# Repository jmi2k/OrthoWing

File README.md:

OrthoWing
=========

- **dimensions**: 229.87mm × 128.27mm
- **layers**: 2

This is a Feather-compatible keyboard. It has a 5×12 ortholinear layout which
makes it very portable and a good fit for exotic use-cases (such as
macro-keyboards). The holes are designed for Cherry MX-compatible switches,
with no extra features.

Usage
-----

Both Feather sockets are interconnected, just like [Adafruit's FeatherWing
Doubler](https://www.adafruit.com/products/2890). The chip sockets hold two
MCP23017 I/O expanders, one on the left to select the column and one on the
right to get the keys pressed on each row for that column.

A controller Feather must also be attached, which scan the key matrix using
these two expanders through I²C. With the help of the second socket and
stacking headers, lots of FeatherWings can be added to provide additional
features!

Use cases
---------

Given a suitable controller (like this [Adafruit Feather
32u4](https://www.adafruit.com/product/2771)), it can be a regular USB
keyboard!

If you want something more exotic, I encourage you to try to push the limits
of the Feather interface! There are compatible displays, sensors, wireless
transceivers, even [quite powerful
FPGAs](https://github.com/gregdavill/OrangeCrab). The keyboard itself doesn't
use any GPIO pins, just the I²C pins (which are shared among all devices
attached), so these are all free.

License
-------

This project is licensed under the [Creative Commons Attribution-ShareAlike
4.0 International License](http://creativecommons.org/licenses/by-sa/4.0/).

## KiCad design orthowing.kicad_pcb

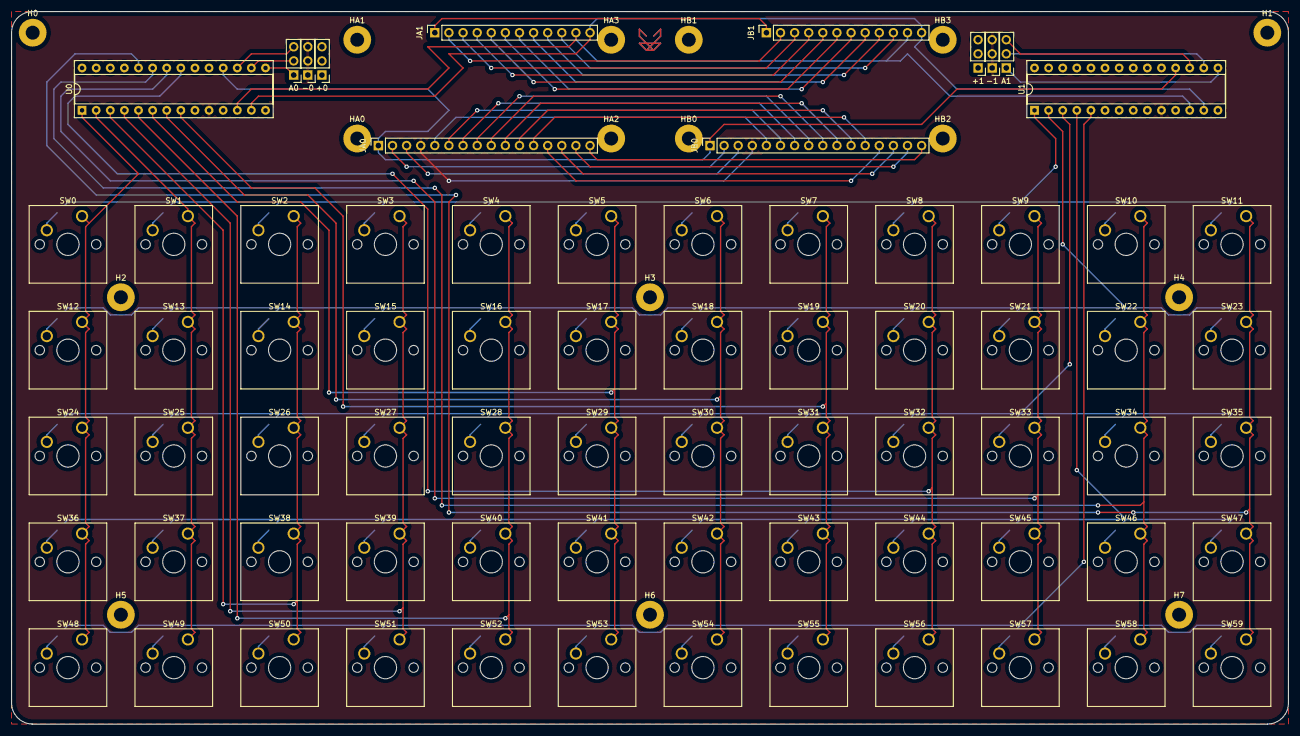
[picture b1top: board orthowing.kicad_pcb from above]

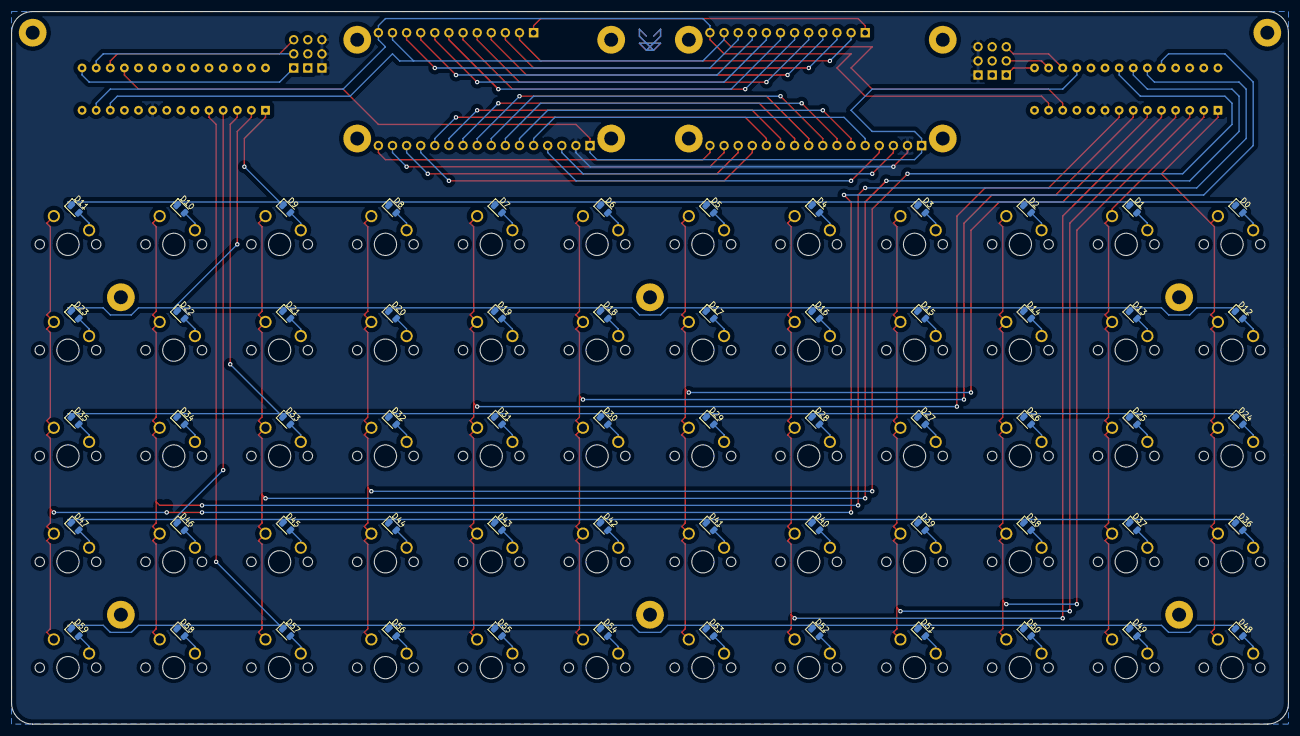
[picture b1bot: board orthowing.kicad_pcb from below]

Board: 2 copper layers, 229.9 x 128.3 mm, 148 parts (60 on the bottom side), 111 nets.

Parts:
+0, +1: Conn_01x03; PinHeader_1x03_P2.54mm_Vertical
-0, -1: Conn_01x03; PinHeader_1x03_P2.54mm_Vertical
A0, A1: Conn_01x03; PinHeader_1x03_P2.54mm_Vertical
D0, D1, D2, D3, D4, D5, D6, D7, D8, D9, D10, D11, D12, D13, D14, D15, D16, D17, D18, D19, D20, D21, D22, D23, D24, D25, D26, D27, D28, D29, D30, D31, D32, D33, D34, D35, D36, D37, D38, D39, D40, D41, D42, D43, D44, D45, D46, D47, D48, D49, D50, D51, D52, D53, D54, D55, D56, D57, D58, D59: D; D_0805_2012Metric
H0, H1, H2, H3, H4, H5, H6, H7: MountingHole; MountingHole_2.5mm_Pad
HA0, HA1, HA2, HA3: MountingHole; MountingHole_2.5mm_Pad
HB0, HB1, HB2, HB3: MountingHole; MountingHole_2.5mm_Pad
JA0: Conn_01x16_Female; PinSocket_1x16_P2.54mm_Vertical
JA1: Conn_01x12_Female; PinSocket_1x12_P2.54mm_Vertical
JB0: Conn_01x16_Female; PinSocket_1x16_P2.54mm_Vertical
JB1: Conn_01x12_Female; PinSocket_1x12_P2.54mm_Vertical
SW0, SW1, SW2, SW3, SW4, SW5, SW6, SW7, SW8, SW9, SW10, SW11, SW12, SW13, SW14, SW15, SW16, SW17, SW18, SW19, SW20, SW21, SW22, SW23, SW24, SW25, SW26, SW27, SW28, SW29, SW30, SW31, SW32, SW33, SW34, SW35, SW36, SW37, SW38, SW39, SW40, SW41, SW42, SW43, SW44, SW45, SW46, SW47, SW48, SW49, SW50, SW51, SW52, SW53, SW54, SW55, SW56, SW57, SW58, SW59: SW_MX; SW_Cherry_MX1A_1.00u_PCB
U0, U1: MCP23017_SP; DIP-28_W7.62mm_Socket

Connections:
0: JA0.14, JB0.14
1: JA0.15, JB0.15
3V3: +0.1, +0.2, +0.3, +1.1, +1.2, +1.3, JA0.2, JB0.2, U0.9, U1.9
5: JA1.10, JB1.10
6: JA1.9, JB1.9
9: JA1.8, JB1.8
10: JA1.7, JB1.7
11: JA1.6, JB1.6
12: JA1.5, JB1.5
13: JA1.4, JB1.4
A0: JA0.5, JB0.5
A1: JA0.6, JB0.6
A2: JA0.7, JB0.7
A3: JA0.8, JB0.8
A4: JA0.9, JB0.9
A5: JA0.10, JB0.10
AREF: JA0.3, JB0.3
C0: SW0.1, SW12.1, SW24.1, SW36.1, SW48.1, U0.1
C1: SW1.1, SW13.1, SW25.1, SW37.1, SW49.1, U0.2
C2: SW2.1, SW14.1, SW26.1, SW38.1, SW50.1, U0.3
C3: SW3.1, SW15.1, SW27.1, SW39.1, SW51.1, U0.4
C4: SW4.1, SW16.1, SW28.1, SW40.1, SW52.1, U0.5
C5: SW5.1, SW17.1, SW29.1, SW41.1, SW53.1, U0.6
C6: SW6.1, SW18.1, SW30.1, SW42.1, SW54.1, U0.7
C7: SW7.1, SW19.1, SW31.1, SW43.1, SW55.1, U0.8
C8: SW8.1, SW20.1, SW32.1, SW44.1, SW56.1, U0.21
C9: SW9.1, SW21.1, SW33.1, SW45.1, SW57.1, U0.22
C10: SW10.1, SW22.1, SW34.1, SW46.1, SW58.1, U0.23
C11: SW11.1, SW23.1, SW35.1, SW47.1, SW59.1, U0.24
EN: JA1.2, JB1.2
GND: -0.1, -0.2, -0.3, -1.1, -1.2, -1.3, JA0.4, JB0.4, U0.10, U1.10
MISO: JA0.13, JB0.13
MOSI: JA0.12, JB0.12
unnamed: A0.1, U0.15
unnamed: A0.2, U0.16
unnamed: A0.3, U0.17
unnamed: A1.1, U1.15
unnamed: A1.2, U1.16
unnamed: A1.3, U1.17
unnamed: D0.2, SW0.2
unnamed: D1.2, SW1.2
unnamed: D2.2, SW2.2
unnamed: D3.2, SW3.2
unnamed: D4.2, SW4.2
unnamed: D5.2, SW5.2
unnamed: D6.2, SW6.2
unnamed: D7.2, SW7.2
unnamed: D8.2, SW8.2
unnamed: D9.2, SW9.2
unnamed: D10.2, SW10.2
unnamed: D11.2, SW11.2
unnamed: D12.2, SW12.2
unnamed: D13.2, SW13.2
unnamed: D14.2, SW14.2
unnamed: D15.2, SW15.2
unnamed: D16.2, SW16.2
unnamed: D17.2, SW17.2
unnamed: D18.2, SW18.2
unnamed: D19.2, SW19.2
unnamed: D20.2, SW20.2
unnamed: D21.2, SW21.2
unnamed: D22.2, SW22.2
unnamed: D23.2, SW23.2
unnamed: D24.2, SW24.2
unnamed: D25.2, SW25.2
unnamed: D26.2, SW26.2
unnamed: D27.2, SW27.2
unnamed: D28.2, SW28.2
unnamed: D29.2, SW29.2
unnamed: D30.2, SW30.2
unnamed: D31.2, SW31.2
unnamed: D32.2, SW32.2
unnamed: D33.2, SW33.2
unnamed: D34.2, SW34.2
unnamed: D35.2, SW35.2
unnamed: D36.2, SW36.2
unnamed: D37.2, SW37.2
unnamed: D38.2, SW38.2
unnamed: D39.2, SW39.2
unnamed: D40.2, SW40.2
unnamed: D41.2, SW41.2
unnamed: D42.2, SW42.2
unnamed: D43.2, SW43.2
unnamed: D44.2, SW44.2
unnamed: D45.2, SW45.2
unnamed: D46.2, SW46.2
unnamed: D47.2, SW47.2
unnamed: D48.2, SW48.2
unnamed: D49.2, SW49.2
unnamed: D50.2, SW50.2
unnamed: D51.2, SW51.2
unnamed: D52.2, SW52.2
unnamed: D53.2, SW53.2
unnamed: D54.2, SW54.2
unnamed: D55.2, SW55.2
unnamed: D56.2, SW56.2
unnamed: D57.2, SW57.2
unnamed: D58.2, SW58.2
unnamed: D59.2, SW59.2
R0: D0.1, D1.1, D2.1, D3.1, D4.1, D5.1, D6.1, D7.1, D8.1, D9.1, D10.1, D11.1, U1.1
R1: D12.1, D13.1, D14.1, D15.1, D16.1, D17.1, D18.1, D19.1, D20.1, D21.1, D22.1, D23.1, U1.2
R2: D24.1, D25.1, D26.1, D27.1, D28.1, D29.1, D30.1, D31.1, D32.1, D33.1, D34.1, D35.1, U1.3
R3: D36.1, D37.1, D38.1, D39.1, D40.1, D41.1, D42.1, D43.1, D44.1, D45.1, D46.1, D47.1, U1.4
R4: D48.1, D49.1, D50.1, D51.1, D52.1, D53.1, D54.1, D55.1, D56.1, D57.1, D58.1, D59.1, U1.5
RST: JA0.1, JB0.1, U0.18, U1.18
SCK: JA0.11, JB0.11
SCL: JA1.11, JB1.11, U0.12, U1.12
SDA: JA1.12, JB1.12, U0.13, U1.13
VBAT: JA1.1, JB1.1
VUSB: JA1.3, JB1.3
X: JA0.16, JB0.16

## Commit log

2020-04-22 Upload to GitHub
2020-04-22 Add render to README
2020-04-27 The keyboard is "ortholinear", not "orthogonal"
2020-04-29 Remove 'keyswitches.pretty' submodule
    Apparently, I wasn't even using it in the first place, as KiCad already
    includes a mechanical switch library. I chose one of them by mistake, but it
    turned out to be an useful mistake.
